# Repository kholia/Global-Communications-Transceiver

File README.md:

# Intro

The `Global Communications Transceiver` project. Global-Communications-Transceiver
is a 5W radio transceiver which is rugged, simple, and reliable.

It is a `optionally silent` digital radio which can be heard almost all over
the world!

Note: Receiving amateur and CB radio traffic without any license is fine in
most countries - please check your local regulations to be sure. Transmitting
on amateur shortwave bands usually requires an amateur radio license but you
are free to transmit and experiment on the CB band.

https://en.wikipedia.org/wiki/Citizens_band_radio_in_India

## Render

## Results

Sample contact from Pune to Medellin on 10m (15691km):

Another sample conact with `WW1WW` (Pune to USA):

## Features

- Single USB-C cable for handling both Audio + CAT control

- True 5W output on all HF bands. It even outputs ~1-2 W @ 50 MHz! (We now just
  need a 6m capable receiver section to build a 6m digital transceiver).

- Rock-solid PA which handles open, short, and bad SWR conditions (1:10 SWR
  tested). We knowingly stress-test it with untuned antennas and still manage
  DX (not a recommended practice for sure though).

- Rock-steady VFO which does NOT drift even under exposed conditions.  Yes - it
  receives WSPR at 28 MHz just fine.

- Reliable T/R switching based on a DPDT relay

- Switchable BPF support to get rid of BCI and other interferences (tested
  against OTH radar + 100 kW AM station in close visual proximity)

- No toroids to wind assuming an external LPF bank is in use ;-)

- The IRF510 final remains as cool as a cucumber (Class-D operation).

- Avoids problems associated with the 'audio frequency counting' approach used
  by earlier designs. Our transceiver has a bit-perfect, deterministic TX output.

- Supports largely automated assembly from JLCPCB (all the required files are
  in the same GitHub repository)

- It comes with a free, open-source AGPLv3 licensed firmware.

- No calibration is (ever) required. Just pick it up and it is ready to go
  on air.

- Low cost (20 to 30 USD is our BOM estimate)

- Stress tested by WSJT-Z for multiple days

- It routinely receives FT8 traffic from 80 to 100+ countries using a simple 5m
  long EFHW antenna

## RX Performance

Performance of CD2003-with-BPF is >= 80% of that of RSP1 SDR, at least!

## TX Performance

## VFO stability

It receives WSPR @ 28 MHz ;)

## WSPR TX Performance

## Files

With these files, you can get around 80% pre-assembled boards (with the SMD
components soldered) from JLCPCB at a minimal cost.

- [BOM](./design-files/HF-PA-v10.csv)

- [Gerbers + PCBA files](./design-files/jlcpcb/production_files)

- [Schematic](./design-files/Schematics.pdf)

Note: The Si5351+TCXO boards can be ordered in fully assembled form from
JLCPCB. https://github.com/kholia/Si5351-Module-Clone-TCXO/ has the required
files (use the `-v4` folder).

JLCPCB link: https://jlcpcb.com/

JLCPCB ordering guide: https://github.com/WB2CBA/ADX-UnO-V1.3/ has the JLCPCB
ordering guide in it.

## Building the firmware (for Linux users)

Shortcut: Upload the pre-built `.uf2` file to the RP2040 Board and skip
to the next section.

Install dependencies:

```
sudo apt install cmake gcc-arm-none-eabi libnewlib-arm-none-eabi \
  libstdc++-arm-none-eabi-newlib git libusb-1.0-0-dev build-essential \
  make g++ gcc
```

```
mkdir ~/repos
cd ~/repos
```

```
git clone --recursive https://github.com/kholia/tinyusb.git  # use this in pico-sdk
git clone --recursive https://github.com/raspberrypi/pico-sdk.git
git clone --recursive https://github.com/kholia/Global-Communications-Transceiver.git
```

Now build the firmware using instructions in the `firmware` folder.

Load the built `.uf2` file into the MCU board. Process: Hold the BOOT button on
RP2040-Zero, and then connect it to a computer. Release the BOOT button. A new
drive will open on the computer. Just drag the .uf2 firmware file (included in
the repository) to this new drive. Done!

## Power sources

The transceiver was tested with the following power sources.

- SUGON 3005D Adjustable Digital DC Power - RECOMMENDED

- 3S "12V" Li-ion 18650 battery pack (RECOMMENDED for field operations)

- RUIDENG DPS5020 power supply module (@13v) powered by MEAN WELL / Mornsun SMPS

## Tips and Hints

- Do NOT use the internal LPF + BPF filters. Just use https://github.com/kholia/DDX/tree/master/RX-TX-BPF-2025-v2 externally.

- IRF510 needs to be insulated from the heat sink.

- You can ignore the `External ATU jack` stuff.

- Use a Common-Mode-Choke (attached between the rig, and the antenna) for
  safety against `return/back RF`.

- DDX works seamlessly with https://play.google.com/store/apps/details?id=com.bunzee.ft8radio app!

## Resources

- The `Global Communications Transceiver` project comes from our DDX family of
  transceiver designs - https://github.com/kholia/DDX/

- https://rf-tools.com/lc-filter/

- https://github.com/WB2CBA/ADX (the design that started it all)

- http://www.learningaboutelectronics.com/Articles/Low-pass-filter-calculator.php

- https://github.com/kholia/ConsensusBasedTimeSync (receiver comes from here)

- https://github.com/kholia/Si5351-Module-Clone-TCXO/ (VFO comes from here)

- https://github.com/kholia/HF-PA-v10 (PA comes from here)

  Ruggedness philosophy: https://www.youtube.com/watch?v=4r7wHMg5Yjg

- https://www.kk5jy.net/three-wire-gp/ (recommended antenna - superb for DX)

- https://github.com/kholia/HF-Balcony-Antenna-System (another portable antenna setup)

- https://github.com/batica81/microphone-library-for-pico (Vojislav's work makes DDX-1 possible)

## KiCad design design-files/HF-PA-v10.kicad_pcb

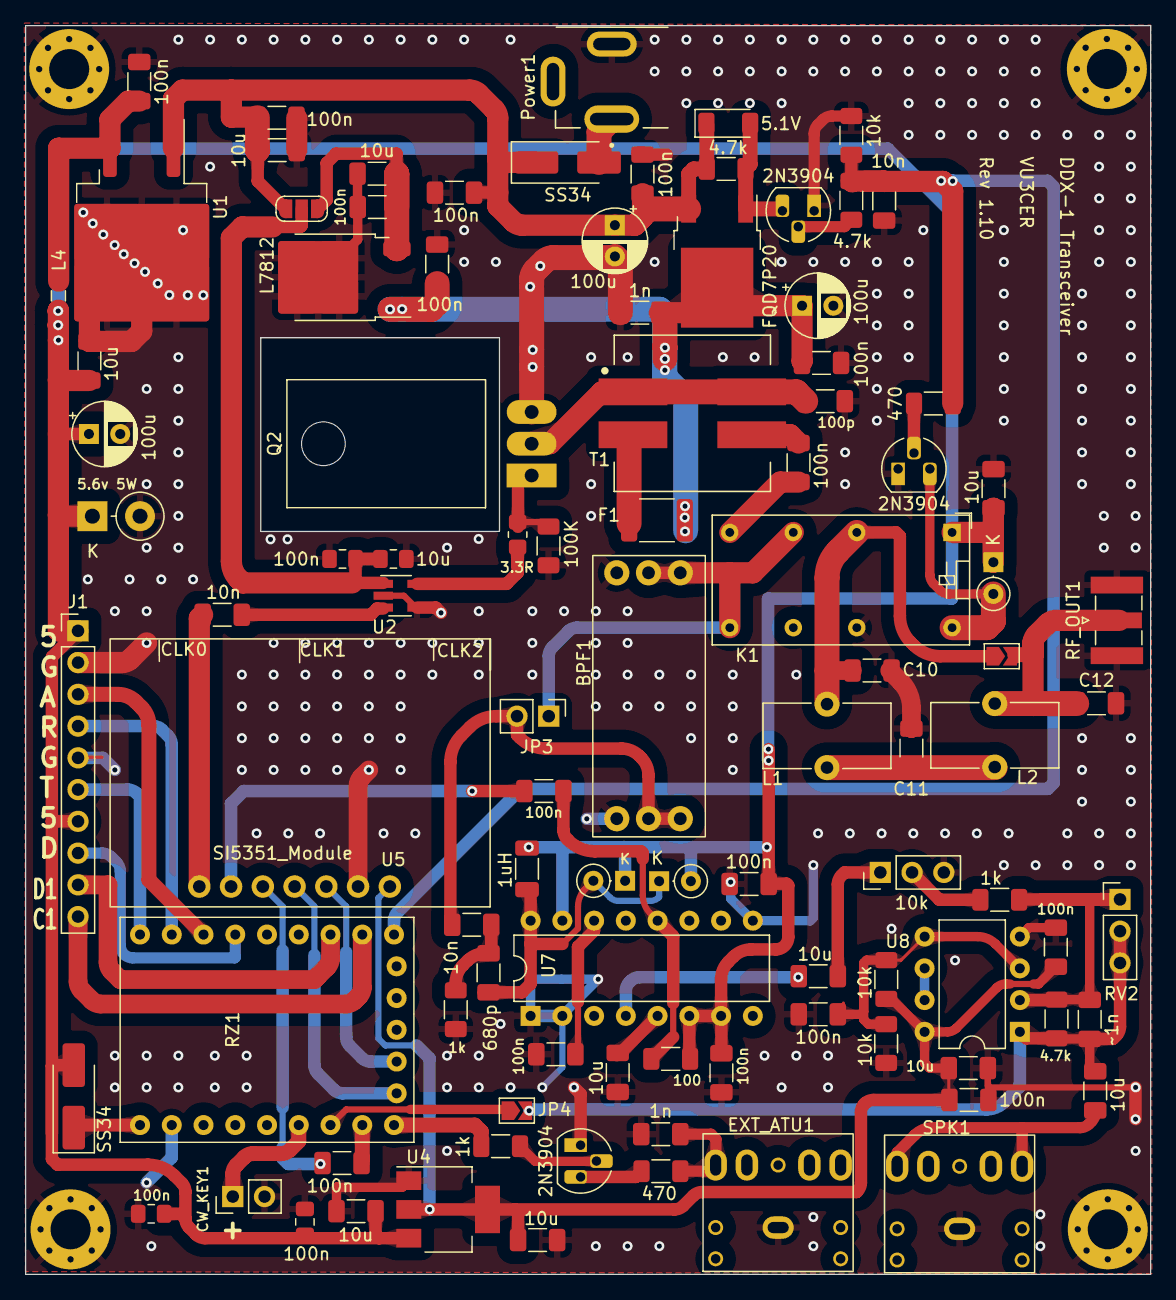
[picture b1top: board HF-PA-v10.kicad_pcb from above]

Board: 2 copper layers, 90.0 x 99.9 mm, 102 parts (0 on the bottom side), 58 nets.

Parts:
BPF1: Pluggable BPF; Pluggable-BPF
C1, C6, C7, C9, C14, C18, C25, C26, C27, C28, C29, C30, C32, C37, C39, C41: 100n; C_1206_3216Metric_Pad1.33x1.80mm_HandSolder
C2, C8, C13, C24, C36, C38, C42, C43, C45, C46: 10u; C_1206_3216Metric_Pad1.33x1.80mm_HandSolder
C3: 100p; C_1206_3216Metric_Pad1.33x1.80mm_HandSolder
C4, C19, C35: 10n; C_1206_3216Metric_Pad1.33x1.80mm_HandSolder
C5, C15, C44: 100u; CP_Radial_D5.0mm_P2.50mm
C10, C12: 120p; C_1206_3216Metric_Pad1.33x1.80mm_HandSolder
C11: 200p; C_1206_3216Metric_Pad1.33x1.80mm_HandSolder
C16: 10u; C_0805_2012Metric_Pad1.18x1.45mm_HandSolder
C17, C20: 1n; C_1206_3216Metric_Pad1.33x1.80mm_HandSolder
C21, C23, C47: 100n; C_0805_2012Metric_Pad1.18x1.45mm_HandSolder
C31: 680p; C_1206_3216Metric_Pad1.33x1.80mm_HandSolder
C40: ~1n; C_1206_3216Metric_Pad1.33x1.80mm_HandSolder
CW_KEY1: Conn_01x02; PinHeader_1x02_P2.54mm_Vertical
D1, D2: SS34; D_SMA_Handsoldering
D3, D8, D9: 1N4148; D_DO-35_SOD27_P2.54mm_Vertical_KathodeUp
D4: 5.1V; D_MiniMELF
D5: 5.6v 5W; D_DO-15_P3.81mm_Vertical_KathodeUp
EXT_ATU1: EXT_ATU; PJ-307_Modded
F1: 2A; Fuse_1812_4532Metric_Pad1.30x3.40mm_HandSolder
H1, H2, H3, H4: MountingHole_Pad; MountingHole_3.2mm_M3_Pad_Via
J1: Conn_01x06; PinHeader_1x10_P2.54mm_Vertical
JP1, JP4: Jumper_2_Open; SolderJumper-2_P1.3mm_Open_TrianglePad1.0x1.5mm
JP2: Power_Switch; SolderJumper-3_P1.3mm_Open_RoundedPad1.0x1.5mm_NumberLabels
JP3: Jumper_2_Open; PinHeader_1x02_P2.54mm_Vertical
K1: Omron G5V-2 / OEN 46-05-2C; Relay_DPDT_Omron_G5V-2
L1, L2: 360n; L_Toroid_Vertical_L10.0mm_W5.0mm_P5.08mm
L4: Ferrite Bead (2A); L_0805_2012Metric_Pad1.05x1.20mm_HandSolder
L5: 1uH; L_1206_3216Metric_Pad1.22x1.90mm_HandSolder
Power1: DC-005 (Barrel Jack); XKB_DC-005-5A-2.0_Modded
Q1, Q4, Q5: 2N3904; TO-92_HandSolder
Q2: IRF510; TO-220-3_Horizontal_TabDown
Q3: FQD7P20; TO-252-2
R1: 100K; R_1206_3216Metric_Pad1.30x1.75mm_HandSolder
R2, R10, R11: 10k; R_1206_3216Metric_Pad1.30x1.75mm_HandSolder
R4: 470; R_1206_3216Metric_Pad1.30x1.75mm_HandSolder
R6: 100; R_1206_3216Metric_Pad1.30x1.75mm_HandSolder
R7: 1k; R_1206_3216Metric_Pad1.30x1.75mm_HandSolder
R8, R9: 4.7k; R_1206_3216Metric_Pad1.30x1.75mm_HandSolder
R12: 3.3R; R_0805_2012Metric_Pad1.20x1.40mm_HandSolder
RF_OUT1: SMA; SMA_Samtec_SMA-J-P-X-ST-EM1_EdgeMount
RV1: 10k; PinHeader_1x03_P2.54mm_Vertical
RV2: 20k; PinHeader_1x03_P2.54mm_Vertical
RZ1: RP2040-Zero
Rb1: 1k; R_1206_3216Metric_Pad1.30x1.75mm_HandSolder
Rf1: 4.7k; R_1206_3216Metric_Pad1.30x1.75mm_HandSolder
Rin1: 1k; R_1206_3216Metric_Pad1.30x1.75mm_HandSolder
Rl1: 470; R_1206_3216Metric_Pad1.30x1.75mm_HandSolder
SPK1: SPEAKER; PJ-307_Modded
T1: Bifilar XFMR; IND_SRF1260A-4R7Y-Longer-Pads
U1: L7805 (D2PAK); TO-263-2
U2: UCC27517ADBVR; SOT-23-5_HandSoldering
U3: L7812; TO-252-2
U4: AMS1117-3.3; SOT-223-3_TabPin2
U5: SI5351_Module; SI5351 Module
U7: CD2003GB_GP; DIP-16_W7.62mm
U8: MCP6002; DIP-8_W7.62mm

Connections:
12V: C1.1, C2.1, C14.1, C15.1, C18.1, D1.1 (K), D4.1 (K), JP2.1 (A), Q3.3 (S), R8.1, U1.1 (IN)
12V_VIA_LDO: C24.1, C30.1, JP2.3 (B), U3.3 (OUT)
+3.3V: C25.1, C41.1, C42.1, C46.1, R10.1, U4.2 (VO), U5.1 (VIN), U8.8 (V+)
+5V: C8.1, C13.1, C21.1, C28.1, C37.1, C44.1, C45.1, C47.1, D2.2 (A), D3.1 (K), D5.1 (K), D8.1 (K), D9.2 (A), J1.1, J1.7, K1.1, L4.1, L5.2, R6.2, U4.3 (VI), U7.6 (VCC), U7.7 (AM_IF), U7.15 (FM_TUNER)
+VDC: D1.2 (A), Power1.1
/DRAIN: C3.1, Q2.2 (D), T1.1, T1.4
ATU: RZ1.15 (GP14), Rb1.1
CAL: C27.2, RZ1.16 (GP15)
CW_KEY: CW_KEY1.1, RZ1.18 (GP27)
GND: BPF1.3 (GND), BPF1.6 (GND), C1.2, C2.2, C3.2, C4.2, C5.2, C6.2, C8.2, C9.2, C10.2, C11.2, C12.2, C13.2, C14.2, C15.2, C16.2, C17.2, C18.2, C20.2, C21.2, C23.2, C24.2, C25.2, C28.2, C29.1, C30.2, C32.2, C36.2, C37.2, C39.2, C41.2, C42.2, C44.2, C45.2, C46.2, C47.2, CW_KEY1.2, D5.2 (A), EXT_ATU1.S, H1.1, H2.1, H3.1, H4.1, J1.2, J1.5, K1.13, Power1.2, Q1.1 (E), Q2.3 (S), Q4.1 (E), Q5.1 (E), R1.2, R2.2, R7.2, R11.2, RF_OUT1.2 (Ext), RV1.3, RZ1.23 (GND), SPK1.S, U1.2 (GND), U2.2 (GND), U2.4 (IN-), U3.2 (GND), U4.1 (GND), U5.2 (GND), U7.1 (FM_RF_IN), U7.2 (GND_IN), U7.9 (GND_OUT), U8.4 (V-)
LDATA: J1.8, RZ1.4 (GP3)
LPF: C10.1, JP1.1 (A), K1.4, L1.1
unnamed: C7.2, T1.3
unnamed: C11.1, L1.2, L2.1
unnamed: C20.1, EXT_ATU1.R, Rl1.1
unnamed: C31.1, C35.1, R7.1
unnamed: C38.2, RV1.1
unnamed: C43.2, SPK1.R, SPK1.T
unnamed: D2.1 (K), RZ1.22 (5V)
unnamed: D3.2 (A), K1.16, Q1.3 (C)
unnamed: D4.2 (A), Q3.1 (G), Q4.3 (C), R8.2
unnamed: C31.2, D8.2 (A), D9.1 (K), L5.1, U7.16 (AM_RF_IN)
unnamed: F1.1, T1.2
unnamed: C12.1, JP1.2 (B), L2.2, RF_OUT1.1 (In)
unnamed: C16.1, C23.1, JP2.2 (C), U2.1 (VDD)
unnamed: JP4.1 (A), RZ1.17 (GP26)
unnamed: Q1.2 (B), R4.2
unnamed: Q2.1 (G), R1.1, R12.2
unnamed: Q4.2 (B), R9.1
unnamed: Q5.2 (B), Rb1.2
unnamed: Q5.3 (C), Rl1.2
unnamed: RV1.2, Rin1.2
unnamed: C9.1, L4.2, U1.3 (OUT)
unnamed: C19.2, U2.3 (IN+)
unnamed: R12.1, U2.5 (OUT)
unnamed: C27.1, U5.5 (S2)
unnamed: C36.1, U7.5 (AGC)
unnamed: C26.1, R6.1, U7.12 (AM_OSC)
unnamed: C29.2, U7.14 (FM/AM_SW)
unnamed: C39.1, R10.2, R11.1, U8.3 (+), U8.5 (+)
unnamed: C40.2, RV2.1, Rf1.2, Rin1.1, U8.2 (-)
unnamed: U8.6 (-), U8.7
PTT: C4.1, R2.1, R4.1, R9.2, RZ1.9 (GP8)
RF_OUT: C7.1, K1.8
RX: BPF1.1 (ANT), BPF1.2 (ANT), JP3.1 (A), K1.6, K1.9
RX_AFTER_HPF: BPF1.4 (RF), BPF1.5 (RF), C35.2, JP3.2 (B)
RX_AUDIO: C38.1, U7.4 (AM_MIX)
RX_OSC: C26.2, U5.6 (S1)
SCL: RZ1.14 (GP13), U5.4 (SCL)
SCL1: J1.10, RZ1.8 (GP7)
SDA: RZ1.13 (GP12), U5.3 (SDA)
SDA1: J1.9, RZ1.7 (GP6)
TO_ADC: C40.1, C43.1, JP4.2 (B), RV2.2, RV2.3, Rf1.1, U8.1
TUNE: J1.3, RZ1.3 (GP2)
TX_RF: C19.1, U5.7 (SO)
UART_RX: J1.4, RZ1.2 (GP1)
UART_TX: J1.6, RZ1.1 (GP0)
VDC_VIA_PTT: C5.1, C6.1, C17.1, C32.1, F1.2, Q3.2 (D), U3.1 (IN)

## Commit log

2024-07-21 The Global Communications Transceiver
2025-07-20 Add some tips
2025-07-20 Compile FW using latest pico-sdk and tinyusb
